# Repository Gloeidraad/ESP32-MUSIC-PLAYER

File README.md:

# ESP32-MUSIC-PLAYER
SD-Card, Webradio, Bluetooth music player based on an ESP32 Wrover module

This is an MP3 player, Web-radio player, Bluetooth player, and simple waveform generator, based on an ESP32 WROVER module. The output can be either a line-out connection or an on-board 2 x 3W @ 4 ohms power ampifier. The output type can be chosen by mounting matching module(s).

This design is derived from my project "AM/FM-modulator-with-ESP32-module" (https://github.com/Gloeidraad/AMFM-modulator-with-ESP32-module). 

The PCB design has been made with KiCad 8.0. 

There at two versions of the design: 
Version 1.1 is mostly based on through hole components. It uses the I2C version of the 2.4 inch OLED display. Some examples can be found at: https://nl.aliexpress.com/item/1005006345983913.html choose the version with the connector on the top and left side of the display. It can be equipped with a PCM5102A Module for line out audio, or with one or two MAX98357A Module(s), allowing to connect directly to loudspeakers with a maximum power of 3 Watt per channel.  
The second version V1.5 is mostly based on 1206 SMD devices, and can be built into a cheap Strapubox 2515WS or the similar TRU COMPONENTS TC-2515 housing, available at https://www.conrad.com. This version uses the SPI version of 2.4 inch OLED display, and supports only audio line output via a PCM5102A Module. The display can also be found on : https://nl.aliexpress.com/item/1005006345983913.html but choose the version  the 7 pins connector on the left side of the display. This version can also be equipped with a SC card adapter, which allows the SD-card to be inserted next to the display. In addition, a nice front cover is available. Both the SD adapter and the front cover are included in the V1.5 design files.
The software will automatically detect, which display is attached, so there is only one version of the software. Please note, that the software supports only ASCII code page 437 (OEM-US, OEM 437, PC-8, or MS-DOS Latin US) up to character 0xAF, so if you enter names and titles with special characters, please be sure that the data is stored in this format. An example of the web radio play list can be found in the project.

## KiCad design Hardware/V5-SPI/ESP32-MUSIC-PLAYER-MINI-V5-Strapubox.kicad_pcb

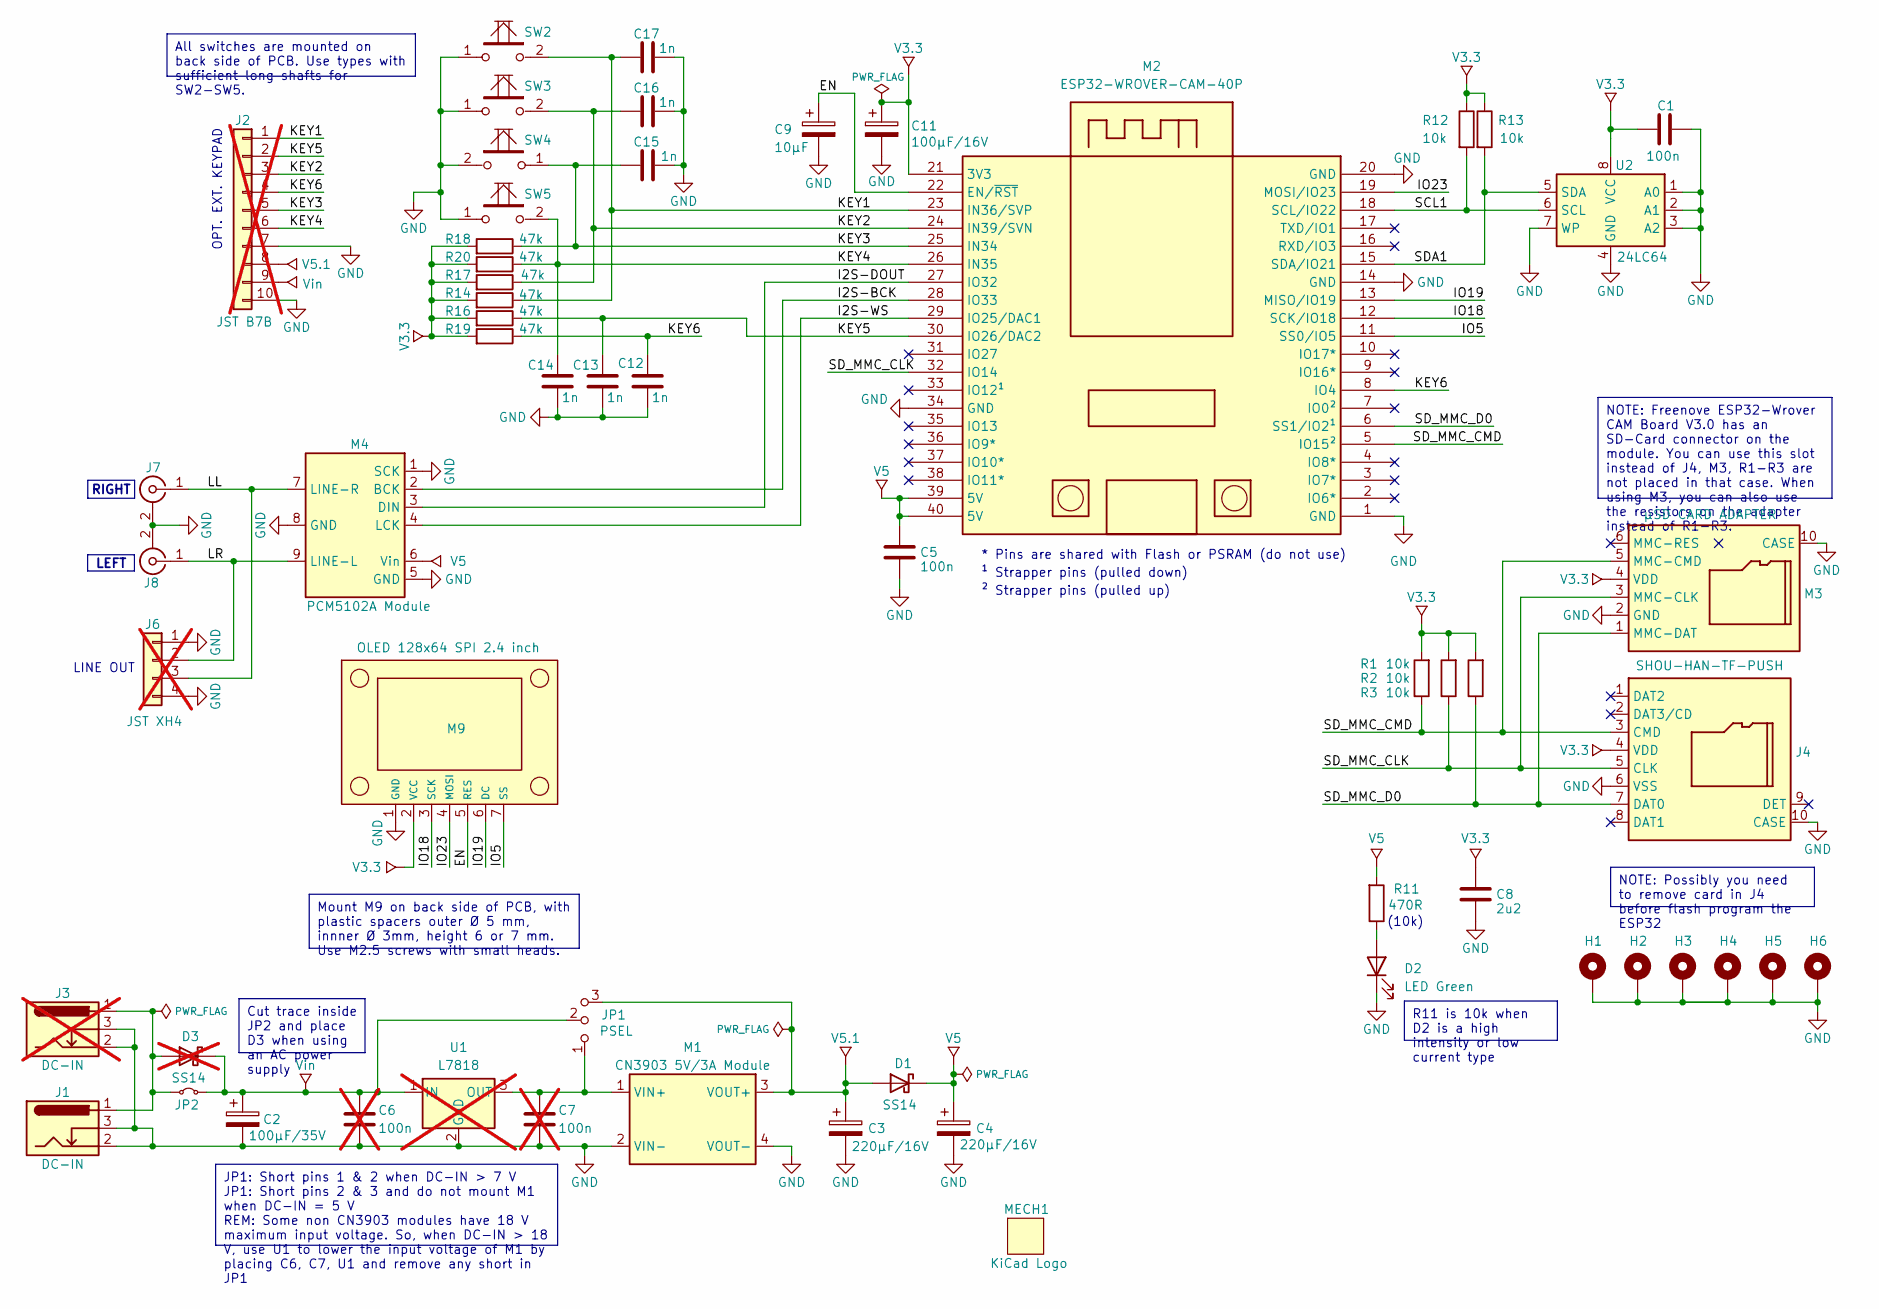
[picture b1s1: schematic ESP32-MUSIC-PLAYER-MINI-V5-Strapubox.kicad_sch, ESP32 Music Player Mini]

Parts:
C1, C5: 100n; C_1206_3216Metric_Pad1.33x1.80mm_HandSolder
C2: 100µF/35V; CE_Radial_D8.0mm_P3.50mm_E2.0mm
C3, C4: 220µF/16V; CE_Radial_D8.0mm_P3.50mm_E2.0mm
C6, C7: 100n; C_1206_3216Metric_Pad1.33x1.80mm_HandSolder; not fitted
C8: 2u2; C_1206_3216Metric_Pad1.33x1.80mm_HandSolder
C9: 10µF; CE_Radial_D6.3mm_P2.50mm_E2.0mm
C11: 100µF/16V; CE_Radial_D6.3mm_P2.50mm_E2.0mm
C12, C13, C14, C15, C16, C17: 1n; C_1206_3216Metric_Pad1.33x1.80mm_HandSolder
D1: SS14; DIODE_SMA
D2: LED Green; LED_D3.0mm
D3: SS14; DIODE_SMA; not fitted
H1, H2, H3, H4, H5, H6: MountingHole; MountingHole_3.7mm_Pad
J1: DC-IN; BarrelJack_GCT_DCJ200-10-A_Horizontal
J2: JST B7B; PinHeader_1x10_P2.54mm_Vertical; not fitted
J3: DC-IN; BarrelJack_GCT_DCJ200-10-A_Horizontal; not fitted
J4: SHOU-HAN-TF-PUSH; TF PUSH; JLC C393941
J6: JST XH4; JST_XH_B4B-XH-A_1x04_P2.50mm_Vertical; not fitted
J7, J8: Keystone 900; Keystone RCA
JP1: PSEL; SolderJumper-3_P1.3mm_Open_RoundedPad1.0x1.5mm
JP2: Jumper_2_Small_Bridged; SolderJumper-2_P1.3mm_Bridged_RoundedPad1.0x1.5mm
M1: CN3903 5V/3A Module; MOD-DC-DC-DUAL
M2: ESP32-WROVER-CAM-40P; ESP32-WROVER-DEV_ON_HEADERS_BARE
M3: µSD CARD ADAPTER; PinHeader_1x06_P2.54mm_SD_expander_socket_T3
M4: PCM5102A Module; MOD-PCM5102A-TYPE2B
M9: OLED 128x64 SPI 2.4 inch; OLED128x64-2.4inch-spi-type1
MECH1: KiCad Logo; KiCad-Logo2_6mm_SilkScreen
R1, R2, R3, R12, R13: 10k; R_1206_3216Metric_Pad1.30x1.75mm_HandSolder
R11: 470R; R_1206_3216Metric_Pad1.30x1.75mm_HandSolder
R14, R16, R17, R18, R19, R20: 47k; R_1206_3216Metric_Pad1.30x1.75mm_HandSolder
SW2, SW3, SW4, SW5: SW-PUSHBUT-6X6-V; SW_TH_Tactile_Omron_B3F-10xx
U1: L7818; TO-252-2; not fitted
U2: 24LC64; SO-8_3.9x4.9mm_P1.27mm

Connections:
/EN: C9.1, M2.22 (EN/~RST), M9.5 (RES)
/I2S-BCK: M2.28 (IO33), M4.2 (BCK)
/I2S-DOUT: M2.27 (IO32), M4.3 (DIN)
/I2S-WS: M2.29 (IO25/DAC1), M4.4 (LCK)
/IO5: M2.11 (SS0/IO5), M9.7 (SS)
/IO18: M2.12 (SCK/IO18), M9.3 (SCK)
/IO19: M2.13 (MISO/IO19), M9.6 (DC)
/IO23: M2.19 (MOSI/IO23), M9.4 (MOSI)
/KEY1: C17.1, J2.1, M2.23 (IN36/SVP), R14.1, SW2.2
/KEY2: C16.1, J2.3, M2.24 (IN39/SVN), R17.1, SW3.2
/KEY3: C15.1, J2.5, M2.25 (IN34), R18.1, SW4.1
/KEY4: C14.1, J2.6, M2.26 (IN35), R20.1, SW5.2
/KEY5: C13.1, J2.2, M2.30 (IO26/DAC2), R16.1
/KEY6: C12.1, J2.4, M2.8 (IO4), R19.1
/LL: J6.3, J7.1 (In), M4.7 (LINE-R)
/LR: J6.2, J8.1 (In), M4.9 (LINE-L)
/SCL1: M2.18 (SCL/IO22), R12.2, U2.6 (SCL)
/SDA1: M2.15 (SDA/IO21), R13.2, U2.5 (SDA)
/SD_MMC_CLK: J4.5 (CLK), M2.32 (IO14), M3.3 (MMC-CLK), R2.1
/SD_MMC_CMD: J4.3 (CMD), M2.5 (IO15²), M3.5 (MMC-CMD), R1.1
/SD_MMC_D0: J4.7 (DAT0), M2.6 (SS1/IO2¹), M3.1 (MMC-DAT), R3.1
GND: C1.2, C2.2, C3.2, C4.2, C5.2, C6.2, C7.2, C8.2, C9.2, C11.2, C12.2, C13.2, C14.2, C15.2, C16.2, C17.2, D2.1 (K), H1.1, H2.1, H3.1, H4.1, H5.1, H6.1, J1.2, J1.3, J2.7, J2.10, J3.2, J3.3, J4.6 (VSS), J4.10 (CASE), J6.1, J6.4, J7.2 (Ext), J8.2 (Ext), M1.2 (VIN-), M1.4 (VOUT-), M2.1 (GND), M2.14 (GND), M2.20 (GND), M2.34 (GND), M3.2 (GND), M3.10 (CASE), M4.1 (SCK), M4.5 (GND), M4.8 (GND), M9.1 (GND), SW2.1, SW3.1, SW4.2, SW5.1, U1.2 (GND), U2.1 (A0), U2.2 (A1), U2.3 (A2), U2.4 (GND), U2.7 (WP)
unnamed: D2.2 (A), R11.1
unnamed: D3.2 (A), J1.1, J3.1, JP2.1 (A)
unnamed: C7.1, JP1.1 (A), M1.1 (VIN+), U1.3 (OUT)
V3.3: C1.1, C8.1, C11.1, J4.4 (VDD), M2.21 (3V3), M3.4 (VDD), M9.2 (VCC), R1.2, R2.2, R3.2, R12.1, R13.1, R14.2, R16.2, R17.2, R18.2, R19.2, R20.2, U2.8 (VCC)
V5: C4.1, C5.1, D1.1 (K), M2.39 (5V), M2.40 (5V), M4.6 (Vin), R11.2
V5.1: C3.1, D1.2 (A), J2.8, JP1.3 (B), M1.3 (VOUT+)
Vin: C2.1, C6.1, D3.1 (K), J2.9, JP1.2 (C), JP2.2 (B), U1.1 (IN)

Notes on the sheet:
R11 is 10k when D2 is a high intensity or low current type
NOTE: Possibly you need to remove card in J4 before flash program the ESP32
All switches are mounted on back side of PCB. Use types with sufficient long shafts for SW2-SW5.
Mount M9 on back side of PCB, with plastic spacers outer Ø 5 mm, innner Ø 3mm, height 6 or 7 mm. Use M2.5 screws with small heads.
NOTE: Freenove ESP32-Wrover CAM Board V3.0 has an SD-Card connector on the module. You can use this slot instead of J4, M3, R1-R3 are not placed in that case. When using M3, you can also use the resistors on the adapter instead of R1-R3.
Cut trace inside JP2 and place D3 when using an AC power supply
JP1: Short pins 1 & 2 when DC-IN > 7 V JP1: Short pins 2 & 3 and do not mount M1 when DC-IN = 5 V REM: Some non CN3903 modules have 18 V maximum input voltage. So, when DC-IN > 18 V, use U1 to lower the input voltage of M1 by placing C6, C7, U1 and remove any short in JP1
² Strapper pins (pulled up)
* Pins are shared with Flash or PSRAM (do not use)
LINE OUT
OPT. EXT. KEYPAD
¹ Strapper pins (pulled down)
RIGHT
(10k)
LEFT

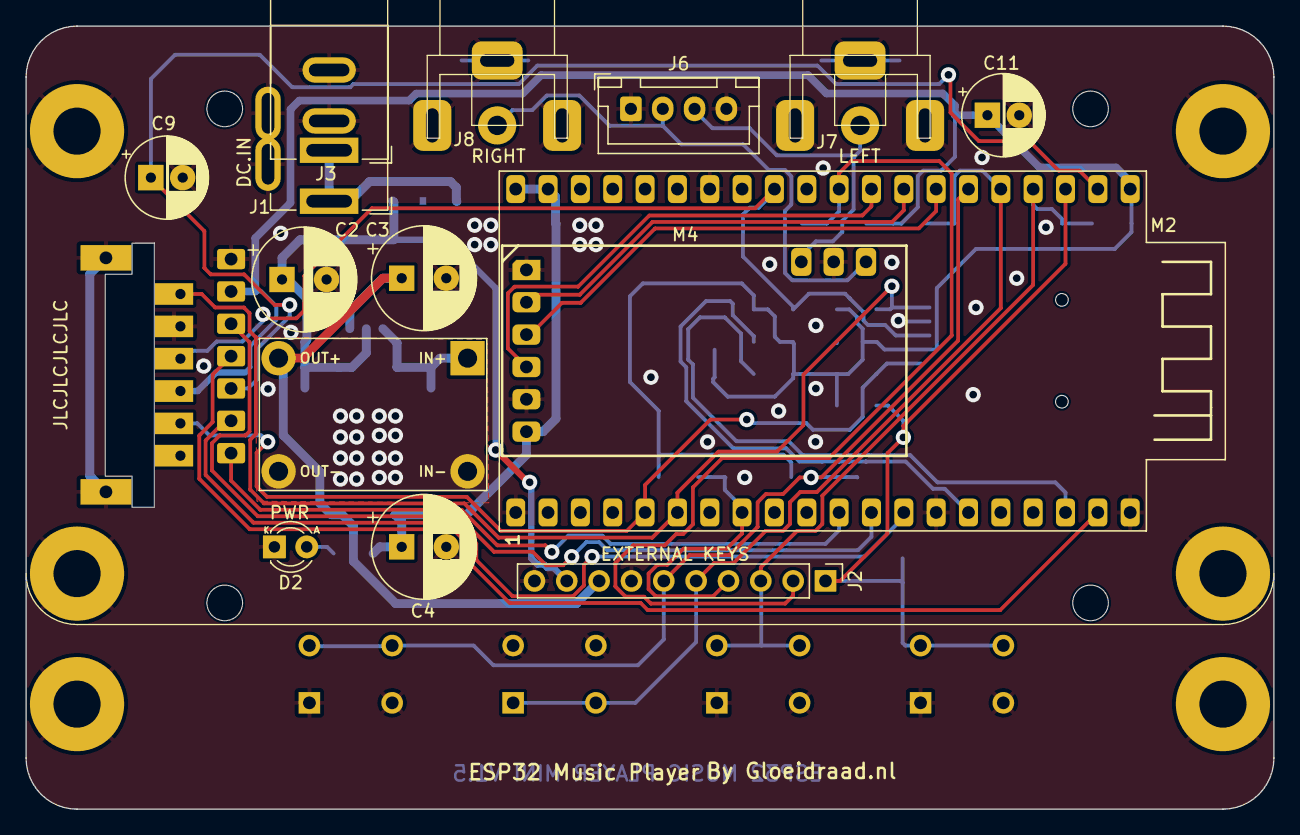
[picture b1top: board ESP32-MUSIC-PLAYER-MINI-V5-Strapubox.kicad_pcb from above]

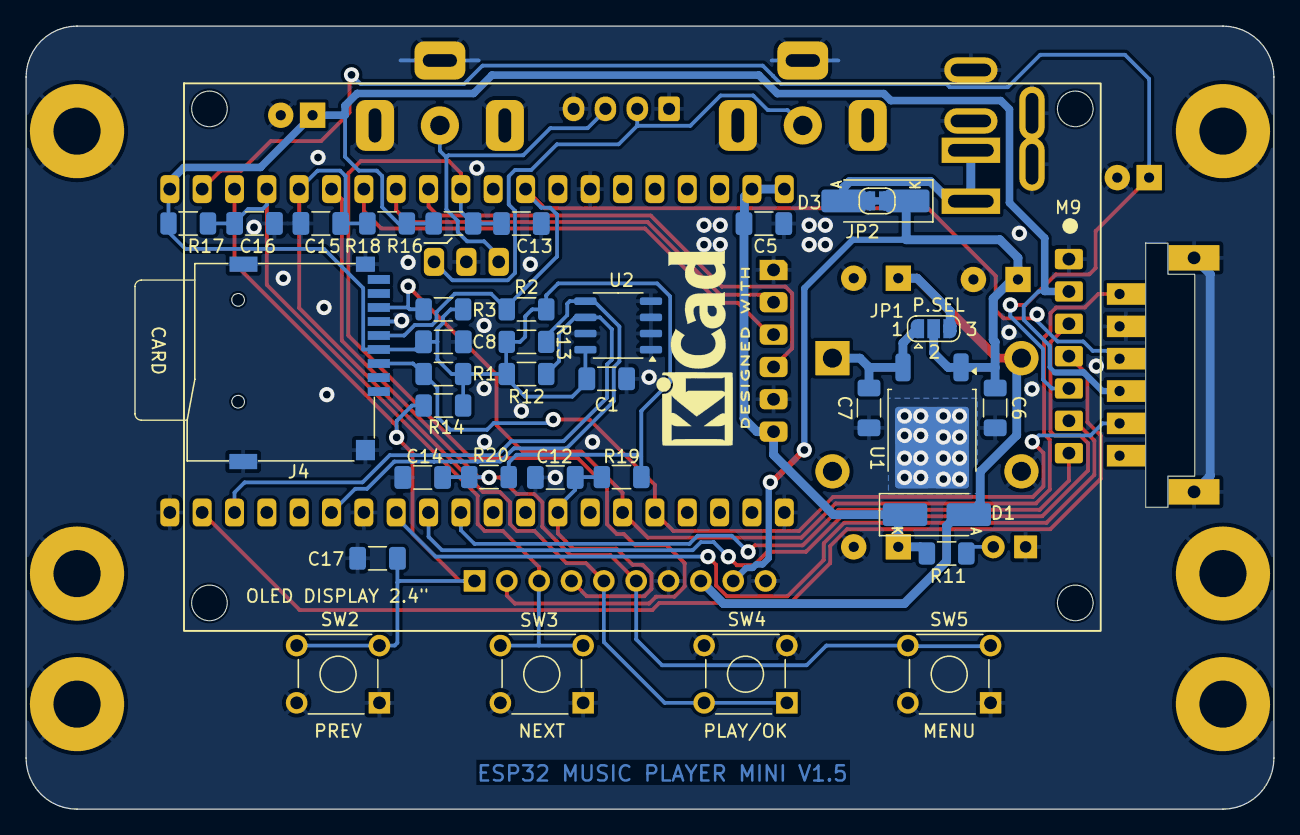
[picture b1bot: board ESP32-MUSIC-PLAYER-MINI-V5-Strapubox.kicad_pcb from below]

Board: 2 copper layers, 98.0 x 61.5 mm, 58 parts (37 on the bottom side), 29 nets.

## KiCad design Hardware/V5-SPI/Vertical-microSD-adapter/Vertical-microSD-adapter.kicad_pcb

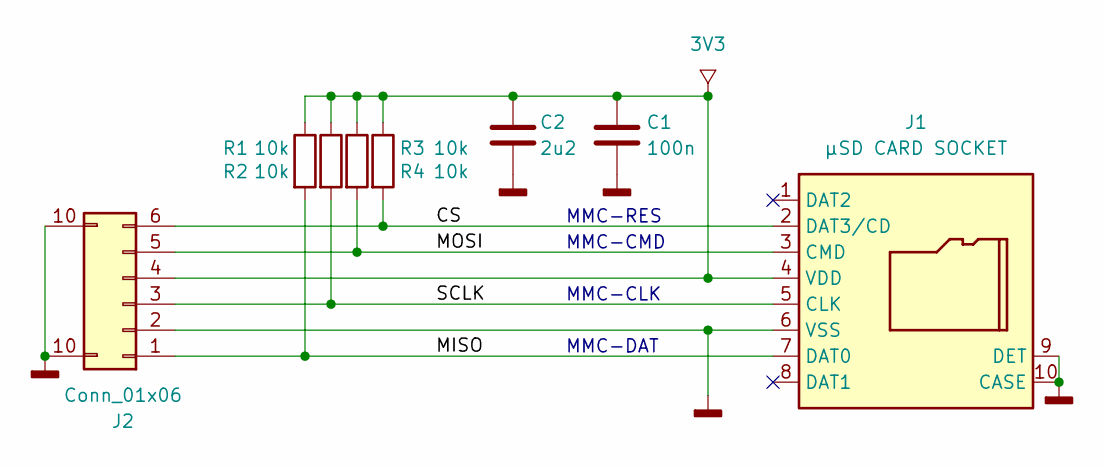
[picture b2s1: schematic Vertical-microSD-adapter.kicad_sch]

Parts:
C1: 100n; C_0603_1608Metric_Pad1.08x0.95mm_HandSolder
C2: 2u2; C_0805_2012Metric_Pad1.18x1.45mm_HandSolder
J1: µSD CARD SOCKET; TF PUSH
J2: Conn_01x06; PinHeader_1x06_P2.54mm_SD_expander
R1, R2, R3, R4: 10k; R_0603_1608Metric_Pad0.98x0.95mm_HandSolder

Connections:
3V3: C1.1, C2.1, J1.4 (VDD), J2.4, R1.1, R2.1, R3.1, R4.1
/CS: J1.2 (DAT3/CD), J2.6, R4.2
/MISO: J1.7 (DAT0), J2.1, R1.2
/MOSI: J1.3 (CMD), J2.5, R3.2
/SCLK: J1.5 (CLK), J2.3, R2.2
GNDD: C1.2, C2.2, J1.6 (VSS), J1.9 (DET), J1.10 (CASE), J2.2, J2.10 (Pin_10a)

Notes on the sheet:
MMC-CMD
MMC-DAT
MMC-CLK
MMC-RES

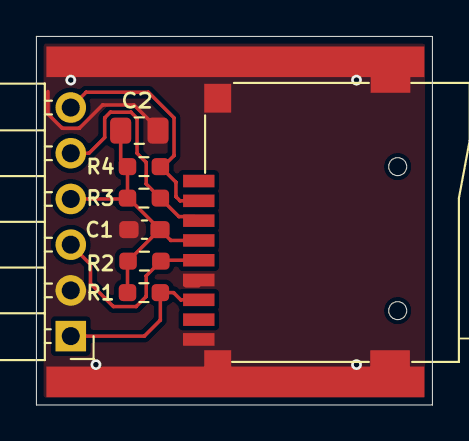
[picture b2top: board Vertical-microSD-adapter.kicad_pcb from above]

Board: 2 copper layers, 22.0 x 20.5 mm, 8 parts (0 on the bottom side), 6 nets.

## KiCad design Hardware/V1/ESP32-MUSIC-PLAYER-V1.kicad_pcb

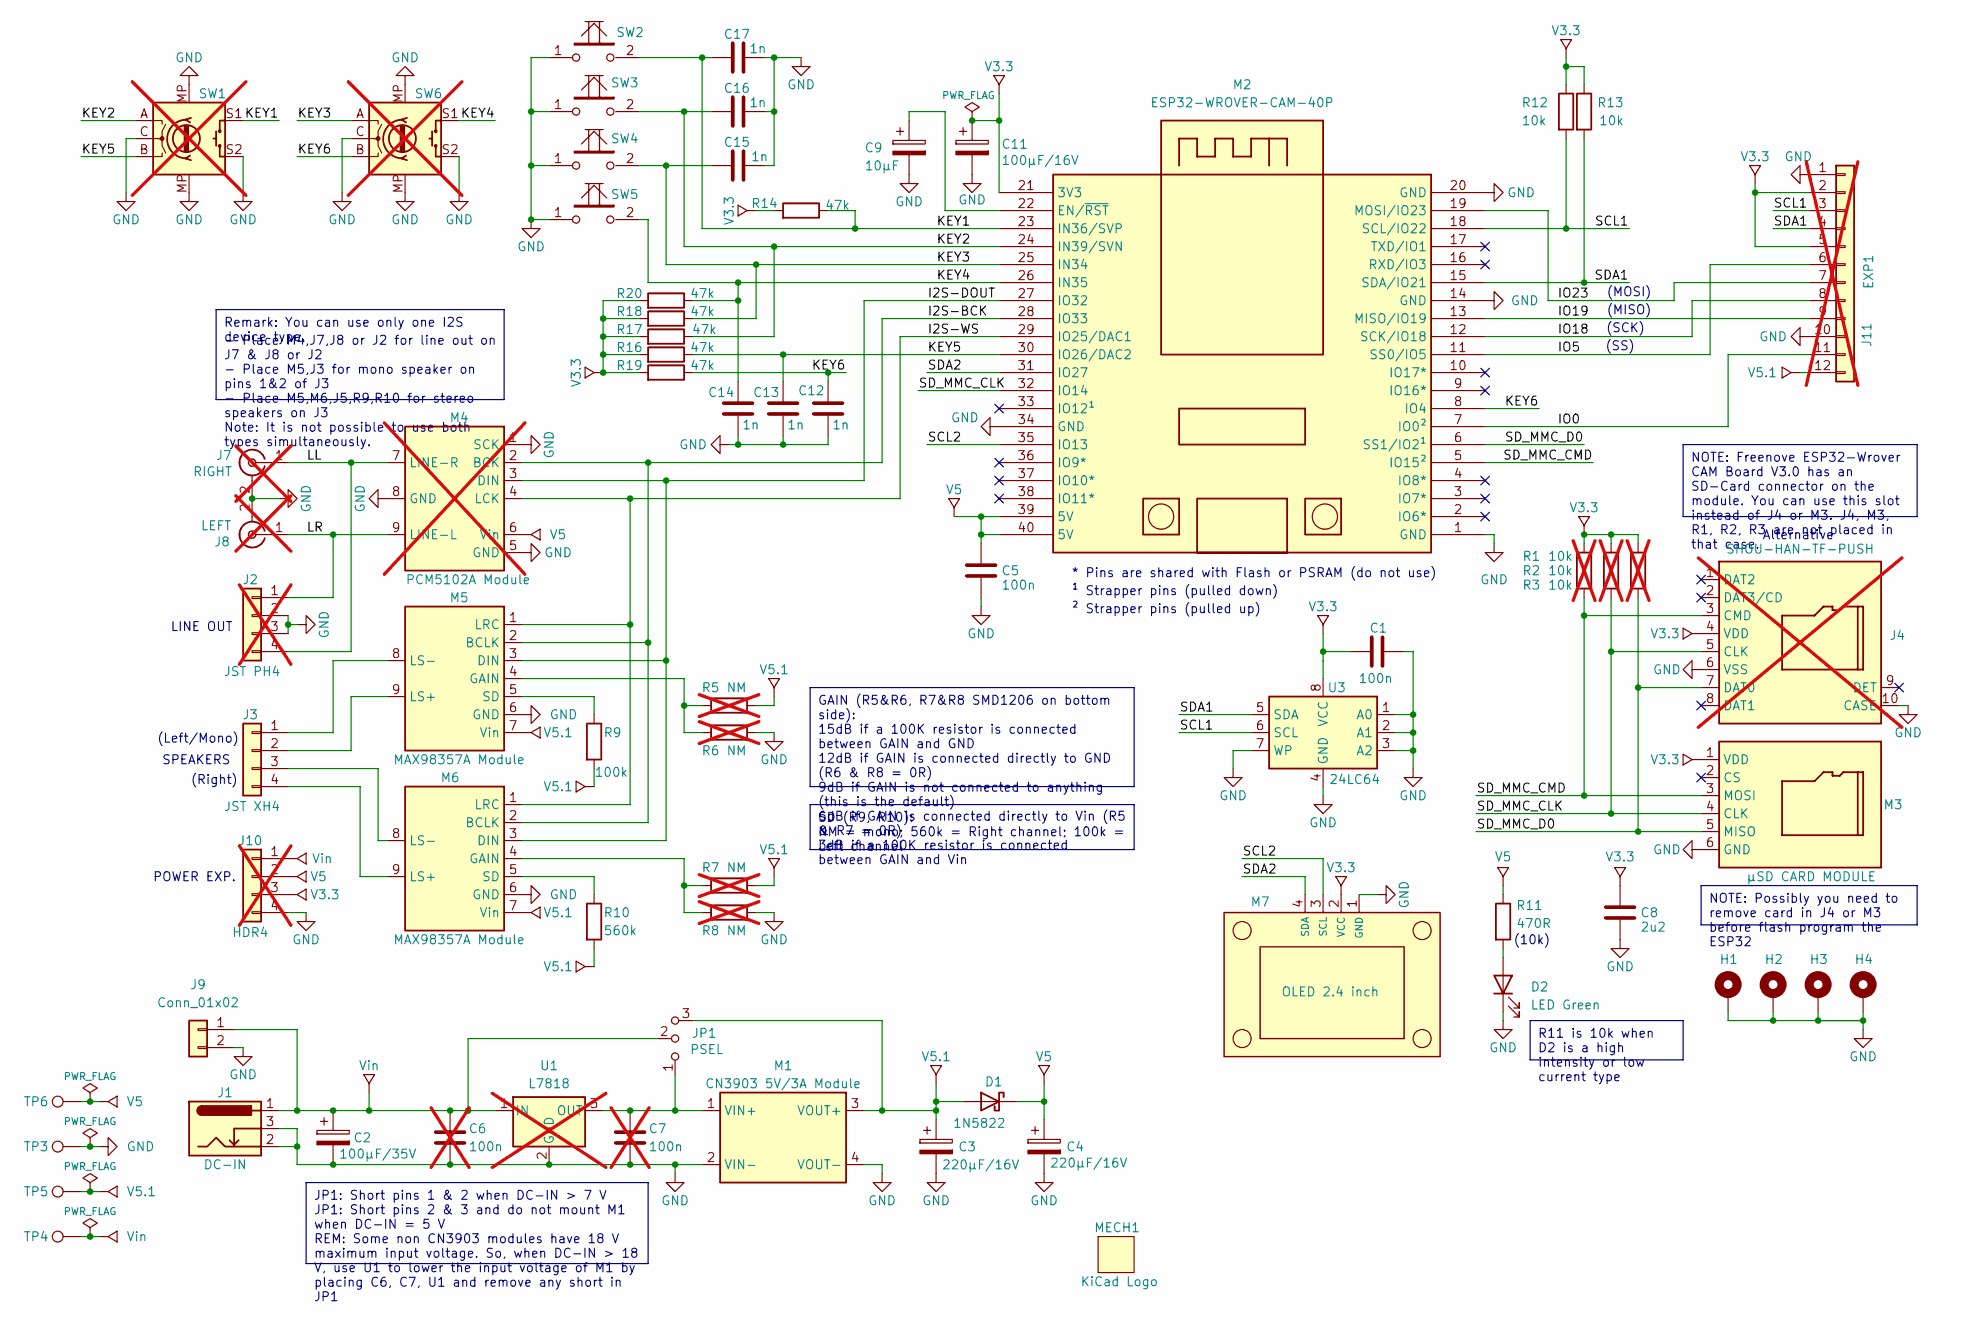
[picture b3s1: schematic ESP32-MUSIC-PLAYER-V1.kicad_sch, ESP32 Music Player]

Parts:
C1, C5: 100n; C_CER_D30_W16_P25_E20_H08
C2: 100µF/35V; CE_Radial_D8.0mm_P3.50mm_E2.0mm
C3, C4: 220µF/16V; CE_Radial_D8.0mm_P3.50mm_E2.0mm
C6, C7: 100n; C_CER_D30_W16_P25_E20_H08; not fitted
C8: 2u2; C_CER_D50_W25_P50_E20_H08
C9: 10µF; CE_Radial_D6.3mm_P2.50mm_E2.0mm
C11: 100µF/16V; CE_Radial_D6.3mm_P2.50mm_E2.0mm
C12, C13, C14, C15, C16, C17: 1n; C_CER_D30_W16_P25_E20_H08
D1: 1N5822; D_DO-201AD_P12.70mm_Horizontal
D2: LED Green; LED_D3.0mm
H1, H2, H3, H4: MountingHole; MountingHole_3.2mm_M3_DIN965_Pad
J1: DC-IN; BarrelJack_GCT_DCJ200-10-A_Horizontal
J2: JST PH4; JST_PH_B4B-PH-K_1x04_P2.00mm_Vertical; not fitted
J3: JST XH4; JST_XH_B4B-XH-A_1x04_P2.50mm_Vertical
J4: SHOU-HAN-TF-PUSH; TF PUSH; JLC C393941; not fitted
J7, J8: Keystone 900; Keystone RCA; not fitted
J9: Conn_01x02; JST_EH_B2B-EH-A_1x02_P2.50mm_Vertical
J10: HDR4; PinHeader_1x04_P2.54mm_Vertical; not fitted
J11: EXP1; PinHeader_1x12_P2.54mm_Vertical; not fitted
JP1: PSEL; PinHeader_1x03_P2.54mm_Vertical
M1: CN3903 5V/3A Module; MOD-DC-DC-DUAL
M2: ESP32-WROVER-CAM-40P; ESP32-WROVER-DEV_ON_HEADERS_BARE
M3: µSD CARD MODULE; MOD-USD-ADAPTER18X18
M4: PCM5102A Module; MOD-PCM5102A-TYPE2B; not fitted
M5, M6: MAX98357A Module; MOD-MAX98357A
M7: OLED 2.4 inch; OLED128x64-2.4inch-i2c-top
MECH1: KiCad Logo; KiCad-Logo2_6mm_SilkScreen
R1, R2, R3: 10k; R_1206_3216Metric_Pad1.30x1.75mm_HandSolder; not fitted
R5, R6, R7, R8: NM; R_1206_3216Metric_Pad1.30x1.75mm_HandSolder; not fitted
R9: 100k; R_Axial_L6.0mm_D2.0mm_P10.16mm_Horizontal
R10: 560k; R_Axial_L6.0mm_D2.0mm_P10.16mm_Horizontal
R11: 470R; R_Axial_L6.0mm_D2.0mm_P10.16mm_Horizontal
R12, R13: 10k; R_Axial_L6.0mm_D2.0mm_P10.16mm_Horizontal
R14, R16, R17, R18, R19, R20: 47k; R_Axial_L6.0mm_D2.0mm_P10.16mm_Horizontal
SW1, SW6: RotaryEncoder_Switch; RotaryEncoder_Bourns_Vertical_PEC12R-3x17F-Sxxxx; not fitted
SW2, SW3, SW4, SW5: SW-PUSHBUT-6X6-V; SW_TH_Tactile_Omron_B3F-10xx
TP3, TP4, TP5, TP6: TestPoint; TestPoint_THTPad_D2.0mm_Drill1.0mm
U1: L7818; TO-220-3_Horizontal_TabDown; not fitted
U3: 24LC64; DIP-SO-08_W7.62mm

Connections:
/I2S-BCK: M2.28 (IO33), M4.2 (BCK), M5.2 (BCLK), M6.2 (BCLK)
/I2S-DOUT: M2.27 (IO32), M4.3 (DIN), M5.3 (DIN), M6.3 (DIN)
/I2S-WS: M2.29 (IO25/DAC1), M4.4 (LCK), M5.1 (LRC), M6.1 (LRC)
/IO0: J11.11, M2.7 (IO0²)
/IO5: J11.6, M2.11 (SS0/IO5)
/IO18: J11.8, M2.12 (SCK/IO18)
/IO19: J11.9, M2.13 (MISO/IO19)
/IO23: J11.7, M2.19 (MOSI/IO23)
/KEY1: C17.1, M2.23 (IN36/SVP), R14.1, SW1.S1, SW2.2
/KEY2: C16.1, M2.24 (IN39/SVN), R17.1, SW1.A, SW3.2
/KEY3: C15.1, M2.25 (IN34), R18.1, SW4.2, SW6.A
/KEY4: C14.1, M2.26 (IN35), R20.1, SW5.2, SW6.S1
/KEY5: C13.1, M2.30 (IO26/DAC2), R16.1, SW1.B
/KEY6: C12.1, M2.8 (IO4), R19.1, SW6.B
/LL: J2.4, J7.1 (In), M4.7 (LINE-R)
/LR: J2.1, J8.1 (In), M4.9 (LINE-L)
/SCL1: J11.3, M2.18 (SCL/IO22), R12.2, U3.6 (SCL)
/SCL2: M2.35 (IO13), M7.3 (SCL)
/SDA1: J11.4, M2.15 (SDA/IO21), R13.2, U3.5 (SDA)
/SDA2: M2.31 (IO27), M7.4 (SDA)
/SD_MMC_CLK: J4.5 (CLK), M2.32 (IO14), M3.4 (CLK), R2.1
/SD_MMC_CMD: J4.3 (CMD), M2.5 (IO15²), M3.3 (MOSI), R1.1
/SD_MMC_D0: J4.7 (DAT0), M2.6 (SS1/IO2¹), M3.5 (MISO), R3.1
GND: C1.2, C2.2, C3.2, C4.2, C5.2, C6.2, C7.2, C8.2, C9.2, C11.2, C12.2, C13.2, C14.2, C15.2, C16.2, C17.2, D2.1 (K), H1.1, H2.1, H3.1, H4.1, J1.2, J1.3, J2.2, J2.3, J4.6 (VSS), J4.10 (CASE), J7.2 (Ext), J8.2 (Ext), J9.2, J10.4, J11.1, J11.10, M1.2 (VIN-), M1.4 (VOUT-), M2.1 (GND), M2.14 (GND), M2.20 (GND), M2.34 (GND), M3.6 (GND), M4.1 (SCK), M4.5 (GND), M4.8 (GND), M5.6 (GND), M6.6 (GND), M7.1 (GND), R6.2, R8.2, SW1.C, SW1.MP, SW1.S2, SW2.1, SW3.1, SW4.1, SW5.1, SW6.C, SW6.MP, SW6.S2, TP3.1, U1.2 (GND), U3.1 (A0), U3.2 (A1), U3.3 (A2), U3.4 (GND), U3.7 (WP)
unnamed: D2.2 (A), R11.2
unnamed: J3.1, M5.8 (LS-)
unnamed: J3.2, M5.9 (LS+)
unnamed: J3.3, M6.8 (LS-)
unnamed: J3.4, M6.9 (LS+)
unnamed: C7.1, JP1.1 (A), M1.1 (VIN+), U1.3 (OUT)
unnamed: C9.1, M2.22 (EN/~RST)
unnamed: M5.4 (GAIN), R5.1, R6.1
unnamed: M5.5 (SD), R9.1
unnamed: M6.4 (GAIN), R7.1, R8.1
unnamed: M6.5 (SD), R10.1
V3.3: C1.1, C8.1, C11.1, J4.4 (VDD), J10.3, J11.2, J11.5, M2.21 (3V3), M3.1 (VDD), M7.2 (VCC), R1.2, R2.2, R3.2, R12.1, R13.1, R14.2, R16.2, R17.2, R18.2, R19.2, R20.2, U3.8 (VCC)
V5: C4.1, C5.1, D1.1 (K), J10.2, M2.39 (5V), M2.40 (5V), M4.6 (Vin), R11.1, TP6.1
V5.1: C3.1, D1.2 (A), J11.12, JP1.3 (B), M1.3 (VOUT+), M5.7 (Vin), M6.7 (Vin), R5.2, R7.2, R9.2, R10.2, TP5.1
Vin: C2.1, C6.1, J1.1, J9.1, J10.1, JP1.2 (C), TP4.1, U1.1 (IN)

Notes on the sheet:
R11 is 10k when D2 is a high intensity or low current type
NOTE: Possibly you need to remove card in J4 or M3 before flash program the ESP32
Remark: You can use only one I2S device type.
GAIN (R5&R6, R7&R8 SMD1206 on bottom side): 15dB if a 100K resistor is connected between GAIN and GND 12dB if GAIN is connected directly to GND (R6 & R8 = 0R) 9dB if GAIN is not connected to anything (this is the default) 6dB if GAIN is connected directly to Vin (R5 & R7 = 0R) 3dB if a 100K resisto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
NOTE: Freenove ESP32-Wrover CAM Board V3.0 has an SD-Card connector on the module. You can use this slot instead of J4 or M3. J4, M3, R1, R2, R3 are not placed in that case.
- Place M4,J7,J8 or J2 for line out on J7 & J8 or J2 - Place M5,J3 for mono speaker on pins 1&2 of J3 - Place M5,M6,J5,R9,R10 for stereo speakers on J3 Note: It is not possible to use both types simultaneously.
SD (R9, R10): NM = mono; 560k = Right channel; 100k = Left channel
JP1: Short pins 1 & 2 when DC-IN > 7 V JP1: Short pins 2 & 3 and do not mount M1 when DC-IN = 5 V REM: Some non CN3903 modules have 18 V maximum input voltage. So, when DC-IN > 18 V, use U1 to lower the input voltage of M1 by placing C6, C7, U1 and remove any short in JP1
Alternative
² Strapper pins (pulled up)
* Pins are shared with Flash or PSRAM (do not use)
LINE OUT
(MISO)
(SS)
POWER EXP.
¹ Strapper pins (pulled down)
(SCK)
(10k)
(Right)
(MOSI)
SPEAKERS
(Left/Mono)

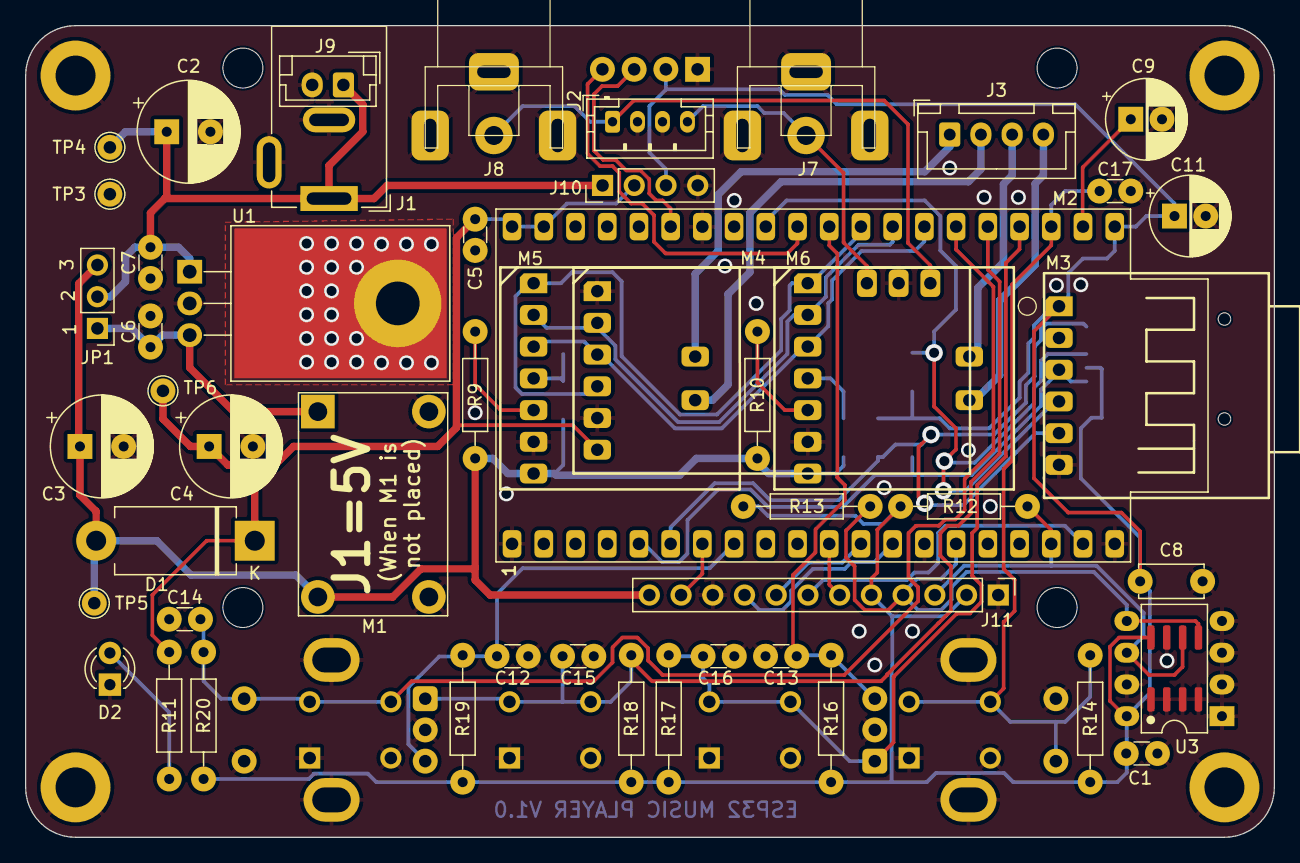
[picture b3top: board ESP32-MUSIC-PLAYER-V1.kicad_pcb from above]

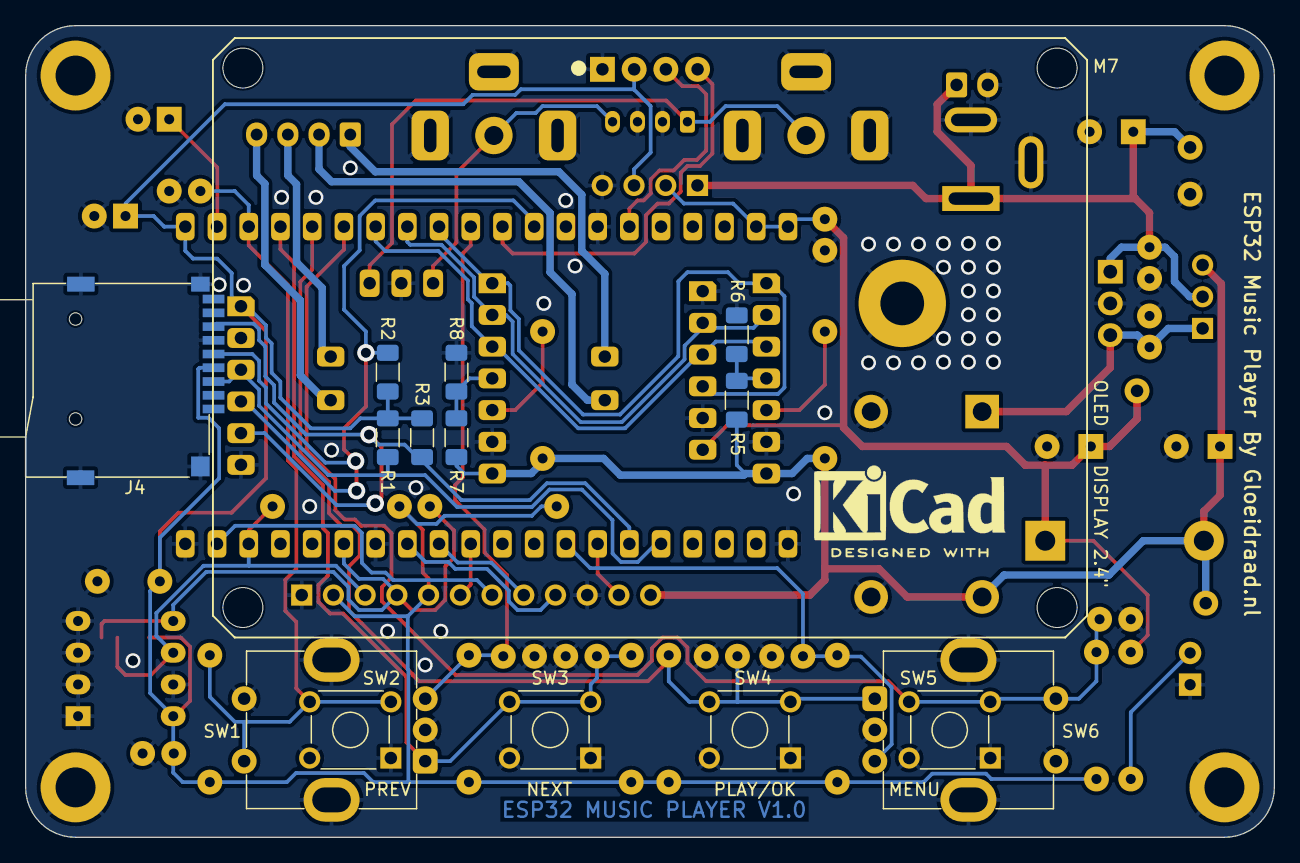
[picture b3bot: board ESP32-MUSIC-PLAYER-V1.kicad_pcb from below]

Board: 2 copper layers, 100.0 x 65.0 mm, 70 parts (16 on the bottom side), 39 nets.

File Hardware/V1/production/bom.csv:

Designator,Footprint,Quantity,Value,LCSC Part #
"C1, C5, C6, C7",C_CER_D30_W16_P25_E20_H08,4,100n,
"C11, C9",CE_Radial_D6.3mm_P2.50mm_E2.0mm,2,10µF,
"C12, C13, C14, C15, C16, C17",C_CER_D30_W16_P25_E20_H08,6,1n,
"C2, C3, C4",CE_Radial_D8.0mm_P3.50mm_E2.0mm,3,100µF,
C8,C_CER_D50_W25_P50_E20_H08,1,2u2,
D1,D_DO-201AD_P12.70mm_Horizontal,1,    1N5822,
D2,LED_D3.0mm,1,LED,
J1,BarrelJack_GCT_DCJ200-10-A_Horizontal,1,DC-IN,
J10,PinHeader_1x04_P2.54mm_Vertical,1,HDR4,
J11,PinHeader_1x12_P2.54mm_Vertical,1,EXP1,
J2,JST_PH_B4B-PH-K_1x04_P2.00mm_Vertical,1,JST PH4,
J3,JST_XH_B4B-XH-A_1x04_P2.50mm_Vertical,1,JST XH4,
J4,TF PUSH,1,SHOU-HAN-TF-PUSH,C393941
"J7, J8",Keystone RCA,2,Keystone 900,
J9,JST_EH_B2B-EH-A_1x02_P2.50mm_Vertical,1,Conn_01x02,
JP1,PinHeader_1x03_P2.54mm_Vertical,1,PSEL,
M1,MOD-DC-DC-DUAL,1,CN3903 5V/3A Module,
M2,ESP32-WROVER-DEV_ON_HEADERS_BARE,1,ESP32-WROVER-CAM-40P,
M3,MOD-USD-ADAPTER18X18,1,µSD CARD MODULE,
M4,MOD-PCM5102A-TYPE2B,1,PCM5102A Module,
"M5, M6",MOD-MAX98357A,2,MAX98357A Module,
M7,OLED128x64-2.4inch-i2c-top,1,OLED 2.4 inch,
"R1, R2, R3",1206,3,10k,
R10,R_Axial_L6.0mm_D2.0mm_P10.16mm_Horizontal,1,560k,
R11,R_Axial_L6.0mm_D2.0mm_P10.16mm_Horizontal,1,470R,
"R12, R13",R_Axial_L6.0mm_D2.0mm_P10.16mm_Horizontal,2,10k,
"R14, R16, R17, R18, R19, R20",R_Axial_L6.0mm_D2.0mm_P10.16mm_Horizontal,6,47k,
"R5, R6, R7, R8",1206,4,NM,
R9,R_Axial_L6.0mm_D2.0mm_P10.16mm_Horizontal,1,100k,
"SW1, SW6",RotaryEncoder_Bourns_Vertical_PEC12R-3x17F-Sxxxx,2,RotaryEncoder_Switch,
"SW2, SW3, SW4, SW5",SW_TH_Tactile_Omron_B3F-10xx,4,SW-PUSHBUT-6X6-V,
"TP3, TP4, TP5, TP6",TestPoint_THTPad_D2.0mm_Drill1.0mm,4,TestPoint,
U1,TO-220-3_Horizontal_TabDown,1,L7818,
U3,DIP-SO-08_W7.62mm,1,24LC64,

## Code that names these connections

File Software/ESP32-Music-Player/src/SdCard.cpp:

#include "SdCard.h"
#include "Settings.h"

#if 1
// MMC-SD: see https://github.com/espressif/arduino-esp32/tree/master/libraries/SD_MMC/src

void InitSdCard(void) {
  #ifdef USE_SD_MMC
    pinMode(SD_MMC_D0, INPUT_PULLUP);
    SD_MMC.setPins(SD_MMC_CLK,SD_MMC_CMD, SD_MMC_D0);
  #else
    pinMode(PIN_SPI_SS, OUTPUT);
    digitalWrite(PIN_SPI_SS, HIGH);
    SPI.begin(PIN_SPI_SCK, PIN_SPI_MISO, PIN_SPI_MOSI);
    SPI.setFrequency(1000000);
  #endif
}

bool MountSdCard(void) {
  #ifdef USE_SD_MMC
    if(!SD_MMC.begin( "/sdcard", true)) {
      Settings.V().NoCard = 1;
      return false;
    }
  #else
    if (!SD.begin(PIN_SPI_SS, SPI, SPI_SD_SPEED)) {
      Settings.V().NoCard = 1;
      return false;
    }
  #endif
  return true;
}

void UnmountSdCard(void) {
  if(Settings.V().NoCard != 1) {
    #ifdef USE_SD_MMC
      SD_MMC.end(); 
    #else
      SD.end();
    #endif
  }
}
#endif

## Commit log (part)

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2024-09-03 Improved volume control for Bluetooth player
    Also cleaned up some files
2024-09-03 Clarification for Freenove ESP32-Wrover CAM Board V3.0
2024-09-18 Renamed V24 to Vin
2024-09-18 Deleted pdf files
    Are now in Doc
2024-09-20 Fixed BT Volume control
2024-09-27 Updated welcome screen
2024-10-04 Added function MenuStringMax()
2024-10-04 Suppress showing ".mp3" entension in SD track titles
2024-10-04 Improved track and URL search
2024-10-05 Updated volume and URL display
2024-11-02 Updated SSD1306 drivers
    Added support for SPI version OLEDs, and some bugfixes
2024-11-09 Updated SPI display support
    Updated SPI drivers. Fixed SPI - Wifi interference bug.
2024-11-09 Accidentally uploaded wrong files
    Now the files are the right ones.
2024-12-20 Update IDE version numbers
2024-12-20 Set i2c as default display interface
    Current hardware supports i2c OLED only. Default was accidentally set to SPI. Changed to i2c.
2024-12-29 Fixed ticker in SSD1306 driver, fixed OLED rotation
2025-02-23 New version with SPI version of 2.4" OLED module
2025-02-23 New version with SPI version of 2.4" OLED module
    Note: this version uses SMD 1206 components.
2025-02-23 Fixed silkscreen location for SW5
2025-02-23 New OLED driver, and support for SPI OLED
    OLED driver now supports proportional fonts. In addition, sketch automatically detects if OLED is on I2C or on SPI bus.
2025-02-24 Expanded SSD1306_FONT_8X8_PROP with code page 437
2025-03-01 Expanded SSD1306_FONT_5X8_PROP with code page 437
    Also fixed some minor bugs
2025-03-01 Example web station file
    Add to the SD Card, insert the card in the ESP32 Music Player, and reboot the player/
2025-03-08 Added limited support for UTF-8 character strings
    Also did some bug fixes
2025-08-25 Added some 3D images of assembly with main PCBA
2025-08-25 Added 2 photos
2025-08-25 Added dimensions for front panel
2025-08-31 Added schematics in PDF
